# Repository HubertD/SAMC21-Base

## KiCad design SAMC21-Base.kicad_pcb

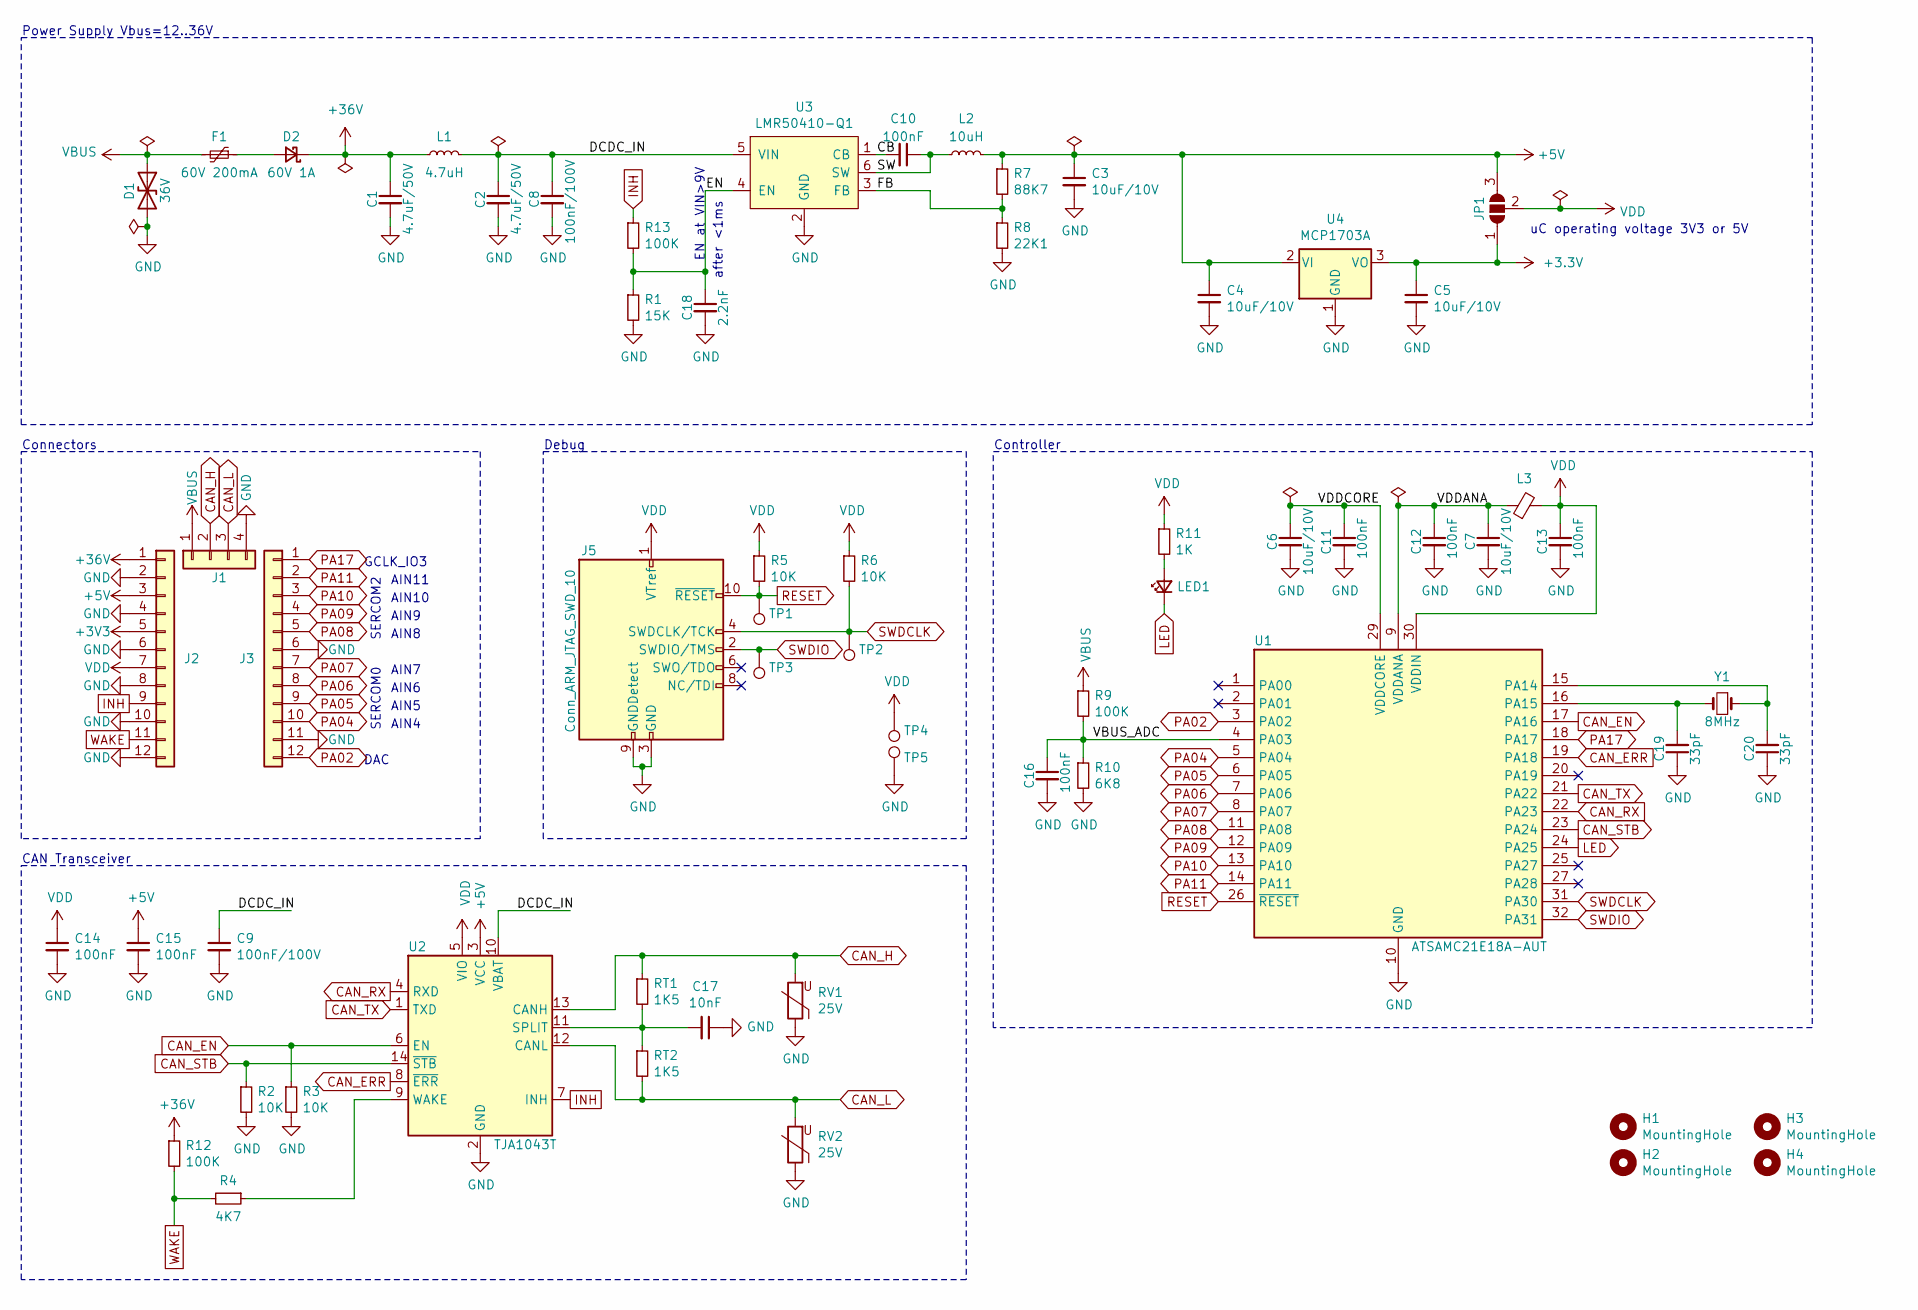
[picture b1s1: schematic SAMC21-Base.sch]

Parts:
C1, C2: 4.7uF/50V; C_1206_3216Metric
C3, C4, C5, C6, C7: 10uF/10V; C_0805_2012Metric
C8, C9: 100nF/100V; C_0603_1608Metric
C10, C11, C12, C13, C14, C15, C16: 100nF; C_0603_1608Metric
C17: 10nF; C_0603_1608Metric
C18: 2.2nF; C_0603_1608Metric
C19, C20: 33pF; C_0603_1608Metric
D1: 36V; D_SMA; MPN SMAJ36CA
D2: 60V 1A; D_SOD-123; MPN RB160MM-60TFTR
F1: 60V 200mA; Fuse_1812_4532Metric; MPN 1812L020/60
H1, H2, H3, H4: MountingHole; MountingHole_2.2mm_M2
J1: Conn_01x04; PinHeader_1x04_P2.54mm_Vertical
J2, J3: Conn_01x10; PinHeader_1x12_P2.54mm_Vertical
J5: Conn_ARM_JTAG_SWD_10; PinHeader_2x05_P1.27mm_Vertical_SMD
JP1: SolderJumper_3_Open; SolderJumper-3_P1.3mm_Open_RoundedPad1.0x1.5mm
L1: 4.7uH; L_0805_2012Metric; MPN MLP2012V4R7MT0S1
L2: 10uH; L_Bourns-SRN4018; MPN SRN4018-100M
L3: 220R@100MHz; L_0603_1608Metric; MPN MPZ1608S221ATA00
LED1: LED_Small; LED_0603_1608Metric
R1: 15K; R_0603_1608Metric
R2, R3, R5, R6: 10K; R_0603_1608Metric
R4: 4K7; R_0603_1608Metric
R7: 88K7; R_0603_1608Metric
R8: 22K1; R_0603_1608Metric
R9, R12, R13: 100K; R_0603_1608Metric
R10: 6K8; R_0603_1608Metric
R11: 1K; R_0603_1608Metric
RT1, RT2: 1K5; R_0805_2012Metric
RV1, RV2: 25V; R_0805_2012Metric; MPN CT0805K25G
TP1, TP2, TP3, TP4, TP5: TestPoint; TestPoint_Pad_D1.5mm
U1: ATSAMC21E18A-AUT; TQFP-32_7x7mm_P0.8mm
U2: TJA1043T; SOIC-14_3.9x8.7mm_P1.27mm
U3: LMR50410-Q1; SOT-23-6
U4: MCP1703A; SOT-89-3
Y1: 8MHz; Crystal_SMD_Abracon_ABM3-2Pin_5.0x3.2mm; MPN ABM3-8.000MHZ-D2Y-T

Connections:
+5V: C3.1, C4.1, C15.1, J2.3, JP1.3 (B), L2.2, R7.1, U2.3 (VCC), U4.2 (VI)
+36V: C1.1, D2.1 (K), J2.1, L1.1, R12.1
/CB: C10.2, U3.1 (CB)
/DCDC_IN: C2.1, C8.1, C9.1, L1.2, U2.10 (VBAT), U3.5 (VIN)
/EN: C18.1, R1.1, R13.2, U3.4 (EN)
/FB: R7.2, R8.1, U3.3 (FB)
/SW: C10.1, L2.1, U3.6 (SW)
/VBUS_ADC: C16.1, R9.2, R10.1, U1.4 (PA03)
/VDDANA: C7.1, C12.1, L3.1, U1.9 (VDDANA)
/VDDCORE: C6.1, C11.1, U1.29 (VDDCORE)
CAN_EN: R3.1, U1.17 (PA16), U2.6 (EN)
CAN_ERR: U1.19 (PA18), U2.8 (~ERR)
CAN_H: J1.2, RT1.1, RV1.2, U2.13 (CANH)
CAN_L: J1.3, RT2.2, RV2.2, U2.12 (CANL)
CAN_RX: U1.22 (PA23), U2.4 (RXD)
CAN_STB: R2.1, U1.23 (PA24), U2.14 (~STB)
CAN_TX: U1.21 (PA22), U2.1 (TXD)
GND: C1.2, C2.2, C3.2, C4.2, C5.2, C6.2, C7.2, C8.2, C9.2, C11.2, C12.2, C13.2, C14.2, C15.2, C16.2, C17.1, C18.2, C19.1, C20.1, D1.2 (A2), J1.4, J2.2, J2.4, J2.6, J2.8, J2.10, J2.12, J3.6, J3.11, J5.3 (GND), J5.5 (GND), J5.9 (GNDDetect), R1.2, R2.2, R3.2, R8.2, R10.2, RV1.1, RV2.1, TP5.1, U1.10 (GND), U1.28 (GND), U2.2 (GND), U3.2 (GND), U4.1 (GND)
INH: J2.9, R13.1, U2.7 (INH)
LED: LED1.1 (K), U1.24 (PA25)
unnamed: C17.2, RT1.2, RT2.1, U2.11 (SPLIT)
unnamed: C19.2, U1.16 (PA15), Y1.2
unnamed: C20.2, U1.15 (PA14), Y1.1
unnamed: D2.2 (A), F1.1
unnamed: LED1.2 (A), R11.2
unnamed: R4.1, U2.9 (WAKE)
PA02: J3.12, U1.3 (PA02)
PA04: J3.10, U1.5 (PA04)
PA05: J3.9, U1.6 (PA05)
PA06: J3.8, U1.7 (PA06)
PA07: J3.7, U1.8 (PA07)
PA08: J3.5, U1.11 (PA08)
PA09: J3.4, U1.12 (PA09)
PA10: J3.3, U1.13 (PA10)
PA11: J3.2, U1.14 (PA11)
PA17: J3.1, U1.18 (PA17)
RESET: J5.10 (~RESET~), R5.2, TP1.1, U1.26 (~RESET)
SWDCLK: J5.4 (SWDCLK/TCK), R6.2, TP2.1, U1.31 (PA30)
SWDIO: J5.2 (SWDIO/TMS), TP3.1, U1.32 (PA31)
VBUS: D1.1 (A1), F1.2, J1.1, R9.1
VDD: C13.1, C14.1, J2.7, J5.1 (VTref), JP1.2 (C), L3.2, R5.1, R6.1, R11.1, TP4.1, U1.30 (VDDIN), U2.5 (VIO)
WAKE: J2.11, R4.2, R12.2

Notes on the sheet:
SERCOM0
AIN4
AIN5
AIN6
AIN7
SERCOM2
AIN8
AIN9
AIN10
AIN11
DAC
GCLK_IO3
Power Supply Vbus=12..36V
Connectors
Debug
CAN Transceiver
Controller
uC operating voltage 3V3 or 5V
EN at VIN>9V
after <1ms

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
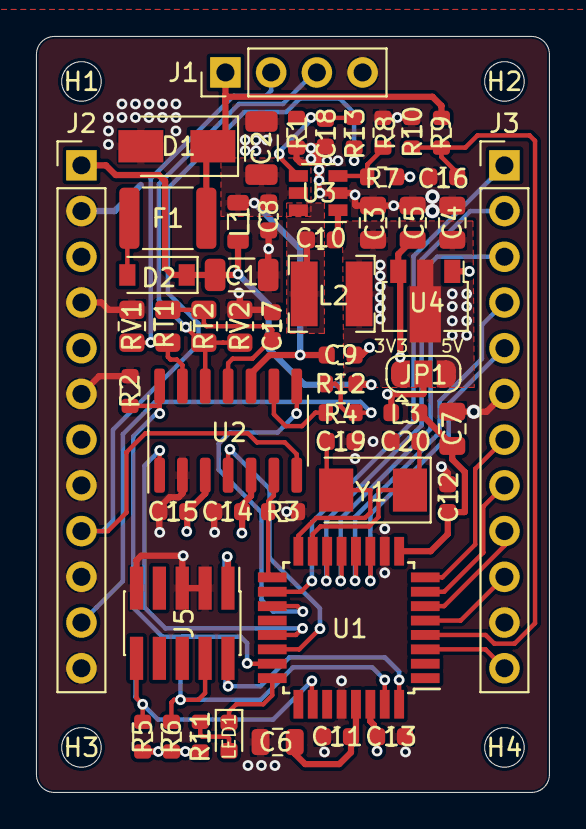
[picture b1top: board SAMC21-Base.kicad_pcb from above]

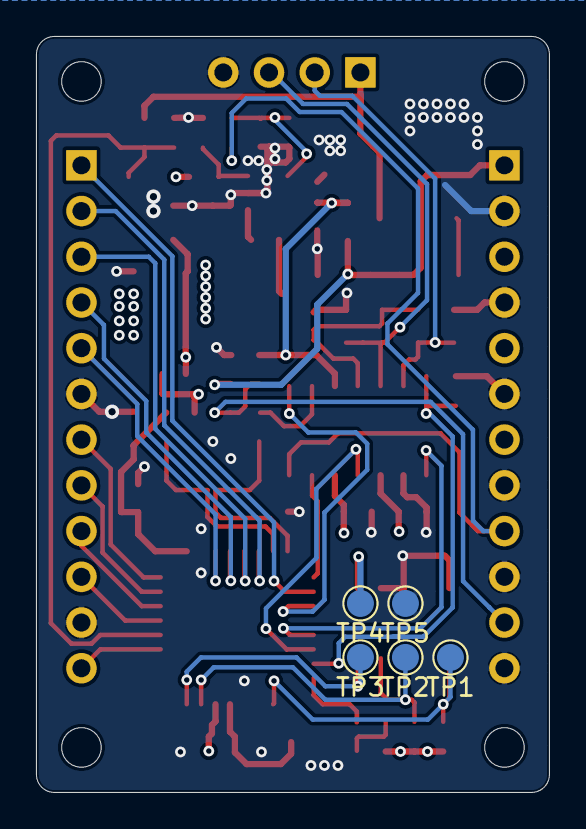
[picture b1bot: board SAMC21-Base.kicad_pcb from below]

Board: 4 copper layers, 28.5 x 42.0 mm, 63 parts (5 on the bottom side), 43 nets.

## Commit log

2021-04-08 initial checkin
2021-04-08 specify ferrite bread
2021-04-08 place ESD protection before polarity protection
2021-04-09 burn less energy on INH-pulldown
2021-04-09 change small VIN capacitor rating to 100V
2021-04-09 connect TJA1043 split pin
2021-04-09 specify crystal and crystal Cs
2021-04-09 improve 3V3 routing
2021-04-09 improve routing
2021-04-09 change VBUS_ACC volatge divider
2021-04-10 add various ESD, EMV and overcurrent protections
2021-04-17 rework power stage, again.
2021-04-18 polish schematics
2021-04-18 redo layout. from scratch.
2021-04-18 minor cleanups
2021-04-19 cleanup after review-3
2021-04-19 use DCDC_IN for TJA1043 Vbat
